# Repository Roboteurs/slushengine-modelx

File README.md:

# SlushEngine Model:X #

This repository contains the hardware design files for the SlusheEngine. The current design is created on Kicad (BZR 5744). If you wish to contribute to the SlusheEngine project please contact Reiner at info at roboteurs dot com.

If you want to get going on your own project using the SlushEngine please fork it and have fun!

## Technical Specifications ##
- Based of L6470 Stepper motor drivers
- Board design to handle 32A on the VPP input
- Supply 5v @ 2A to the Raspberry Pi
- UEXT Connector for expansion modules
- Temperature sensing inputs
- Logic level I/Os and Industrial Level IO (24VDC)
- MAX1164 for temperature sensor handling (2 Channels)
- MCP23017 for I/O expansion on I2C bus
- Raspberry Pi Hat spec eeprom circuit

## Basic Electrical Characteristics ##

- **Max VPP Voltage:** 35VDC
- **Max Current:** 32A
- **No Load Current:** *unkown*
- **Max SPI bus Frequency:** 5Mhz
- **Max Tempratre at L6470L** *unkown*

## Avalible Hardware mods

- **R1010** Can be changed to compensate for off voltage motor (see L6470 datasheet)
- **JP1002** Can be cut to prevent board from powering an expansion module (bottom of the board)

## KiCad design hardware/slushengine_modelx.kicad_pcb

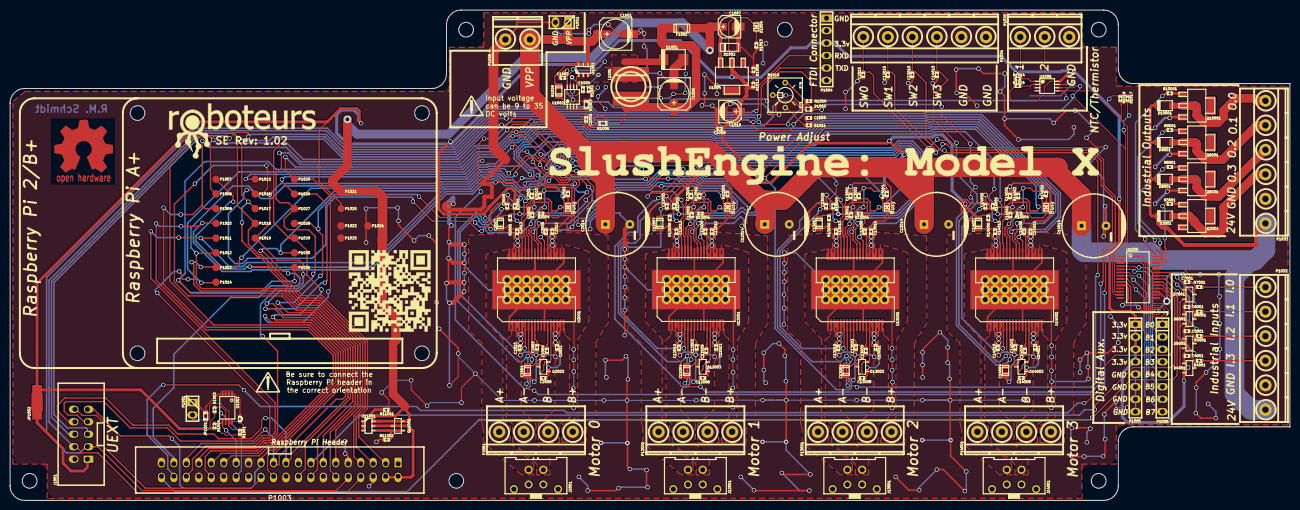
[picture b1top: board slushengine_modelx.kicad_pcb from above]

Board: 2 copper layers, 261.0 x 100.0 mm, 216 parts (0 on the bottom side), 117 nets.

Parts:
C101, C1002, C1005, C1009, C2001, C2002, C2003, C2005, C2006, C2010, C2011, C2012, C2013, C2015, C12001, C12002, C12003, C12005, C12006, C12010, C12011, C12012, C12013, C12015, C13001, C13002, C13003, C13005, C13006, C13010, C13011, C13012, C13013, C13015, C14001, C14002, C14003, C14005, C14006, C14010, C14011, C14012, C14013, C14015: 0.1uf; c_0402
C1001: 50uf/50v; c_elec_6.3x7.7
C1004: 1nf; c_0402
C1006: 100uf/10v; c_elec_6.3x7.7
C1007, C1010: 10uf/6.3V; c_elec_4x5.3
C1008: 33nF; c_0402
C2004, C12004, C13004, C14004: 10uF; c_0805
C2007, C12007, C13007, C14007: 47uF; c_0805
C2008, C12008, C13008, C14008: 220nF; c_0402
C2009, C12009, C13009, C14009: 10nF; c_0402
C2014, C12014, C13014, C14014: 100uF; CP_12.5x25mm
C4001, C5001, C6001, C7001: 1nF; c_0402
D1001: DIODESCH; do214aa
D1002: ZENER; sod80c
D1003: 3.3V; sod523
D1004: LED; Led_0603
D2002, D12002, D13002, D14002: Busy; Led_0603
D2003, D12003, D13003, D14003: DOUBLE_SCHOTTKY; sot23
D3001, D8001, D9001, D10001: RSX501L-20TE25; do219ab
D4001, D5001, D6001, D7001: 1SS295; sot23
F1001: 2A; r_1206
J1001: UEXT1; vasch_strip_5x2
J2001, J12001, J13001, J14001: Stepper Motor; SureStep_CONN
JP1001: JUMPER; r_0603
JP1002: JUMPER; NetTie-I_Connected_SMD
L1001: 22uH; inductor_smd_8x5mm
MountingHole_3mm, MountingHole_3mm#2, MountingHole_3mm#3, MountingHole_3mm#4, MountingHole_3mm#5, MountingHole_3mm#6, MountingHole_3mm#7, MountingHole_3mm#8, MountingHole_3mm#9, MountingHole_3mm#10: VAL**; MountingHole_3mm
P1001, P1002: CONN_01X02; pin_strip_2
P1003: Raspberry_Pi_+_Conn; vasch_strip_20x2
P1004: CONN_01X06; pin_strip_6
P1005, P1006: CONN_01X08; pin_strip_8
P1007, P1008, P1009, P1010, P1011, P1012, P1013, P1014, P1015, P1016, P1017, P1018, P1019, P1020, P1021, P1022, P1023, P1024, P1025, P1026, P1027, P1028, P1029, P1030, P1031: TST; Measurement_Point_Round-SMD-Pad_Small
P1032, P1033, P1034: CONN_01X06; mkds_1,5-6
P1035: CONN_01X03; mkds_1,5-3
P1036: CONN_01X02; mkds_1,5-2
P2001, P12001, P13001, P14001: CONN_01X04; mkds_1,5-4
Q3001, Q8001, Q9001, Q10001: BCP51; sot223
Q11001: DMG2305; sot23
R1001: 1k; r_0402
R1002: 24k; r_0402
R1003, R1004, R1016, R1017: 3.9k; r_0402
R1005: 270; r_0805
R1006: 30k; r_0603
R1007: 10k; r_0603
R1008: 390; r_0402
R1009, R4001, R5001, R6001, R7001: 3.3k; r_0402
R1010: 22k; 25PR20KLF
R1011: 820; r_0402
R1012: 240; r_0402
R1013: 316; r_0402
R1014, R1015: 51k; r_0402
R2002, R2004, R2005, R12002, R12004, R12005, R13002, R13004, R13005, R14002, R14004, R14005: 39k; r_0402
R2003, R12003, R13003, R14003: 220; r_0402
R2006, R11001, R12006, R13006, R14006: 10k; r_0402
R3001, R8001, R9001, R10001: 470; r_0402
R11002: 47k; r_0402
U1001: CAT24C32HU4I-GT3; tssop-8
U1002: LM3489; msoic-8
U1003: FDC5614P; sot23-6
U1004: LM1117IMPX-ADJ; sot223
U1005: MCP23017; ssop-28
U1006: MAX1164x; msoic-8
U2001, U12001, U13001, U14001: L6470; POWERSO-36
U11001: DMMT5401; sot23-6

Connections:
+3V3: C101.1, C1009.1, C1010.1, C2006.1, C2007.1, C12006.1, C12007.1, C13006.1, C13007.1, C14006.1, C14007.1, D1004.1, D4001.3, D5001.3, D6001.3, D7001.3, JP1002.2, P1004.3, P1005.1, P1005.2, P1005.3, P1005.4, P1020.1, R1001.1, R1003.1, R1004.1, R1012.1, R1014.1, R1015.1, R1016.1, R1017.1, R2002.1, R2003.1, R2004.1, R2005.1, R2006.1, R12002.1, R12003.1, R12004.1, R12005.1, R12006.1, R13002.1, R13003.1, R13004.1, R13005.1, R13006.1, R14002.1, R14003.1, R14004.1, R14005.1, R14006.1, U1001.8, U1004.2, U1005.9, U1006.8, U2001.24, U12001.24, U13001.24, U14001.24
+5V: C1007.1, D1002.2, F1001.2, P1021.1, Q11001.3, U1004.3, U11001.6
+24V: C1001.1, C1002.1, C1004.1, C2008.2, C2010.1, C2011.1, C2012.1, C2013.1, C2014.1, C12008.2, C12010.1, C12011.1, C12012.1, C12013.1, C12014.1, C13008.2, C13010.1, C13011.1, C13012.1, C13013.1, C13014.1, C14008.2, C14010.1, C14011.1, C14012.1, C14013.1, C14014.1, D2003.1, D3001.2, D8001.2, D9001.2, D10001.2, D12003.1, D13003.1, D14003.1, P1002.1, P1032.1, P1033.1, P1036.1, R1002.1, R1009.1, U1002.8, U1003.4, U2001.4, U2001.5, U2001.15, U2001.16, U2001.22, U2001.23, U2001.33, U2001.34, U12001.4, U12001.5, U12001.15, U12001.16, U12001.22, U12001.23, U12001.33, U12001.34, U13001.4, U13001.5, U13001.15, U13001.16, U13001.22, U13001.23, U13001.33, U13001.34, U14001.4, U14001.5, U14001.15, U14001.16, U14001.22, U14001.23, U14001.33, U14001.34
/Back Power Protection/5V_MCU: P1003.2, P1003.4, Q11001.2, U11001.5
/IO_EXP_INTA: P1003.40, U1005.20
/IO_EXP_INTB: P1003.15, U1005.19
/IO_EXP_RST: P1003.38, U1005.18
/Industrial Input 0/A/D_Input: P1032.3, R4001.1
/Industrial Input 0/MCU_Input: C4001.1, D4001.2, R4001.2, U1005.21
/Industrial Input 1/A/D_Input: P1032.4, R5001.1
/Industrial Input 1/MCU_Input: C5001.1, D5001.2, R5001.2, U1005.22
/Industrial Input 2/A/D_Input: P1032.5, R6001.1
/Industrial Input 2/MCU_Input: C6001.1, D6001.2, R6001.2, U1005.23
/Industrial Input 3/A/D_Input: P1032.6, R7001.1
/Industrial Input 3/MCU_Input: C7001.1, D7001.2, R7001.2, U1005.24
/Industrial Output 0/MCU_Pin: R3001.1, U1005.25
/Industrial Output 0/Sink: D3001.1, P1033.3, Q3001.2
/Industrial Output 1/MCU_Pin: R8001.1, U1005.26
/Industrial Output 1/Sink: D8001.1, P1033.4, Q8001.2
/Industrial Output 2/MCU_Pin: R9001.1, U1005.27
/Industrial Output 2/Sink: D9001.1, P1033.5, Q9001.2
/Industrial Output 3/MCU_Pin: R10001.1, U1005.28
/Industrial Output 3/Sink: D10001.1, P1033.6, Q10001.2
/PI_I2C_SCL: J1001.5, P1003.5, P1017.1, R1016.2, U1005.12, U1006.5
/PI_I2C_SDA: J1001.6, P1003.3, P1018.1, R1017.2, U1005.13, U1006.6
/PI_SPI_CE0: J1001.10, P1003.24
/PI_UART_RXD: J1001.3, P1003.10, P1004.4
/PI_UART_TXD: J1001.4, P1003.8, P1004.5
/Stepper Driver #0/ADCIN: C1008.1, D1003.2, P1015.1, R1010.2, U2001.8, U12001.8, U13001.8, U14001.8
/Stepper Driver #0/SCK: J1001.9, P1003.23, P1025.1, U2001.26, U12001.26, U13001.26, U14001.26
/Stepper Driver #0/SDI: J1001.8, P1003.19, P1027.1, U2001.27, U12001.27, U13001.27, U14001.27
/Stepper Driver #0/SDO: J1001.7, P1003.21, P1026.1, U2001.25, U12001.25, U13001.25, U14001.25
/Stepper Driver #0/STCK: P1003.7, P1007.1, U2001.32
/Stepper Driver #0/SWITCH: C2015.1, P1034.6, R2006.2, U2001.7
/Stepper Driver #0/VREG: C2003.1, C2004.1, U2001.9
/Stepper Driver #0/~BUSY~/SYNC: C2002.1, D2002.2, P1003.36, P1011.1, R2004.2, U2001.29
/Stepper Driver #0/~CS: P1003.18, P1028.1, U2001.30
/Stepper Driver #0/~FLAG: C2001.1, C12001.1, C13001.1, C14001.1, P1003.33, P1019.1, R2002.2, R12002.2, R13002.2, R14002.2, U2001.31, U12001.31, U13001.31, U14001.31
/Stepper Driver #0/~STBY/RST: C2005.1, C12005.1, C13005.1, C14005.1, P1003.16, P1016.1, R2005.2, R12005.2, R13005.2, R14005.2, U2001.6, U12001.6, U13001.6, U14001.6
/Stepper Driver #1/STCK: P1003.29, P1008.1, U12001.32
/Stepper Driver #1/SWITCH: C12015.1, P1034.5, R12006.2, U12001.7
/Stepper Driver #1/VREG: C12003.1, C12004.1, U12001.9
/Stepper Driver #1/~BUSY~/SYNC: C12002.1, D12002.2, P1003.11, P1012.1, R12004.2, U12001.29
/Stepper Driver #1/~CS: P1003.22, P1029.1, U12001.30
/Stepper Driver #2/STCK: P1003.31, P1009.1, U13001.32
/Stepper Driver #2/SWITCH: C13015.1, P1034.4, R13006.2, U13001.7
/Stepper Driver #2/VREG: C13003.1, C13004.1, U13001.9
/Stepper Driver #2/~BUSY~/SYNC: C13002.1, D13002.2, P1003.12, P1013.1, R13004.2, U13001.29
/Stepper Driver #2/~CS: P1003.37, P1030.1, U13001.30
/Stepper Driver #3/STCK: P1003.32, P1010.1, U14001.32
/Stepper Driver #3/SWITCH: C14015.1, P1034.3, R14006.2, U14001.7
/Stepper Driver #3/VREG: C14003.1, C14004.1, U14001.9
/Stepper Driver #3/~BUSY~/SYNC: C14002.1, D14002.2, P1003.35, P1014.1, R14004.2, U14001.29
/Stepper Driver #3/~CS: P1003.13, P1031.1, U14001.30
GND: C101.2, C1001.2, C1002.2, C1006.2, C1007.2, C1008.2, C1009.2, C1010.2, C2001.2, C2002.2, C2003.2, C2004.2, C2005.2, C2006.2, C2007.2, C2010.2, C2011.2, C2012.2, C2013.2, C2014.2, C2015.2, C4001.2, C5001.2, C6001.2, C7001.2, C12001.2, C12002.2, C12003.2, C12004.2, C12005.2, C12006.2, C12007.2, C12010.2, C12011.2, C12012.2, C12013.2, C12014.2, C12015.2, C13001.2, C13002.2, C13003.2, C13004.2, C13005.2, C13006.2, C13007.2, C13010.2, C13011.2, C13012.2, C13013.2, C13014.2, C13015.2, C14001.2, C14002.2, C14003.2, C14004.2, C14005.2, C14006.2, C14007.2, C14010.2, C14011.2, C14012.2, C14013.2, C14014.2, C14015.2, D1001.1, D1002.1, D1003.1, D4001.1, D5001.1, D6001.1, D7001.1, J1001.2, JP1001.2, P1001.1, P1002.2, P1003.6, P1003.9, P1003.14, P1003.20, P1003.25, P1003.30, P1003.34, P1003.39, P1004.1, P1005.5, P1005.6, P1005.7, P1005.8, P1022.1, P1023.1, P1024.1, P1032.2, P1033.2, P1034.1, P1034.2, P1035.1, P1036.2, Q3001.3, Q8001.3, Q9001.3, Q10001.3, R1007.2, R1008.2, R1011.2, R1013.2, R11001.2, R11002.2, U1001.1, U1001.2, U1001.3, U1001.4, U1002.2, U1002.6, U1005.10, U1005.15, U1005.16, U1005.17, U1006.7, U2001.1, U2001.12, U2001.19, U2001.28, U2001.PAD, U12001.1, U12001.12, U12001.19, U12001.28, U12001.PAD, U13001.1, U13001.12, U13001.19, U13001.28, U13001.PAD, U14001.1, U14001.12, U14001.19, U14001.28, U14001.PAD
unnamed: C1004.2, R1002.2, U1002.5
unnamed: C1005.1, C1006.1, F1001.1, L1001.2, R1006.1
unnamed: C1005.2, R1006.2, R1007.1, U1002.4
unnamed: C2008.1, D2003.3, U2001.14
unnamed: C2009.1, D2003.2
unnamed: C2009.2, U2001.13
unnamed: C12008.1, D12003.3, U12001.14
unnamed: C12009.1, D12003.2
unnamed: C12009.2, U12001.13
unnamed: C13008.1, D13003.3, U13001.14
unnamed: C13009.1, D13003.2
unnamed: C13009.2, U13001.13
unnamed: C14008.1, D14003.3, U14001.14
unnamed: C14009.1, D14003.2
unnamed: C14009.2, U14001.13
unnamed: D1001.2, L1001.1, R1005.1, U1003.1, U1003.2, U1003.5, U1003.6
unnamed: D1004.2, R1013.1
unnamed: D2002.1, R2003.2
unnamed: D12002.1, R12003.2
unnamed: D13002.1, R13003.2
unnamed: D14002.1, R14003.2
unnamed: J1001.1, JP1002.1
unnamed: J2001.1, P2001.1, U2001.35, U2001.36
unnamed: J2001.2, P2001.2, U2001.2, U2001.3
unnamed: J2001.3, P2001.3, U2001.17, U2001.18
unnamed: J2001.4, P2001.4, U2001.20, U2001.21
unnamed: J12001.1, P12001.1, U12001.35, U12001.36
unnamed: J12001.2, P12001.2, U12001.2, U12001.3
unnamed: J12001.3, P12001.3, U12001.17, U12001.18
unnamed: J12001.4, P12001.4, U12001.20, U12001.21
unnamed: J13001.1, P13001.1, U13001.35, U13001.36
unnamed: J13001.2, P13001.2, U13001.2, U13001.3
unnamed: J13001.3, P13001.3, U13001.17, U13001.18
unnamed: J13001.4, P13001.4, U13001.20, U13001.21
unnamed: J14001.1, P14001.1, U14001.35, U14001.36
unnamed: J14001.2, P14001.2, U14001.2, U14001.3
unnamed: J14001.3, P14001.3, U14001.17, U14001.18
unnamed: J14001.4, P14001.4, U14001.20, U14001.21
unnamed: JP1001.1, P1001.2, R1001.2, U1001.7
unnamed: P1003.27, R1004.2, U1001.5
unnamed: P1003.28, R1003.2, U1001.6
unnamed: P1006.1, U1005.1
unnamed: P1006.2, U1005.2
unnamed: P1006.3, U1005.3
unnamed: P1006.4, U1005.4
unnamed: P1006.5, U1005.5
unnamed: P1006.6, U1005.6
unnamed: P1006.7, U1005.7
unnamed: P1006.8, U1005.8
unnamed: P1035.2, R1015.2, U1006.2
unnamed: P1035.3, R1014.2, U1006.1
unnamed: Q3001.1, R3001.2
unnamed: Q8001.1, R8001.2
unnamed: Q9001.1, R9001.2
unnamed: Q10001.1, R10001.2
unnamed: Q11001.1, R11002.1, U11001.4
unnamed: R1005.2, U1002.1
unnamed: R1008.1, R1012.2, U1004.1
unnamed: R1009.2, R1010.1
unnamed: R1010.3, R1011.1
unnamed: R11001.1, U11001.1, U11001.2, U11001.3
unnamed: U1002.7, U1003.3

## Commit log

2015-06-15 simple updates
2015-06-15 inital file commit
2015-06-15 added some new part numbers
2015-06-15 fixed pour issue by removing chamfers
2015-06-15 added board photo
2015-06-15 small board changes
2015-06-15 initial commit of contrib file
